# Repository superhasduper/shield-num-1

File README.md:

# shield-num-1
it is an Arduino shield pcb made in kicad

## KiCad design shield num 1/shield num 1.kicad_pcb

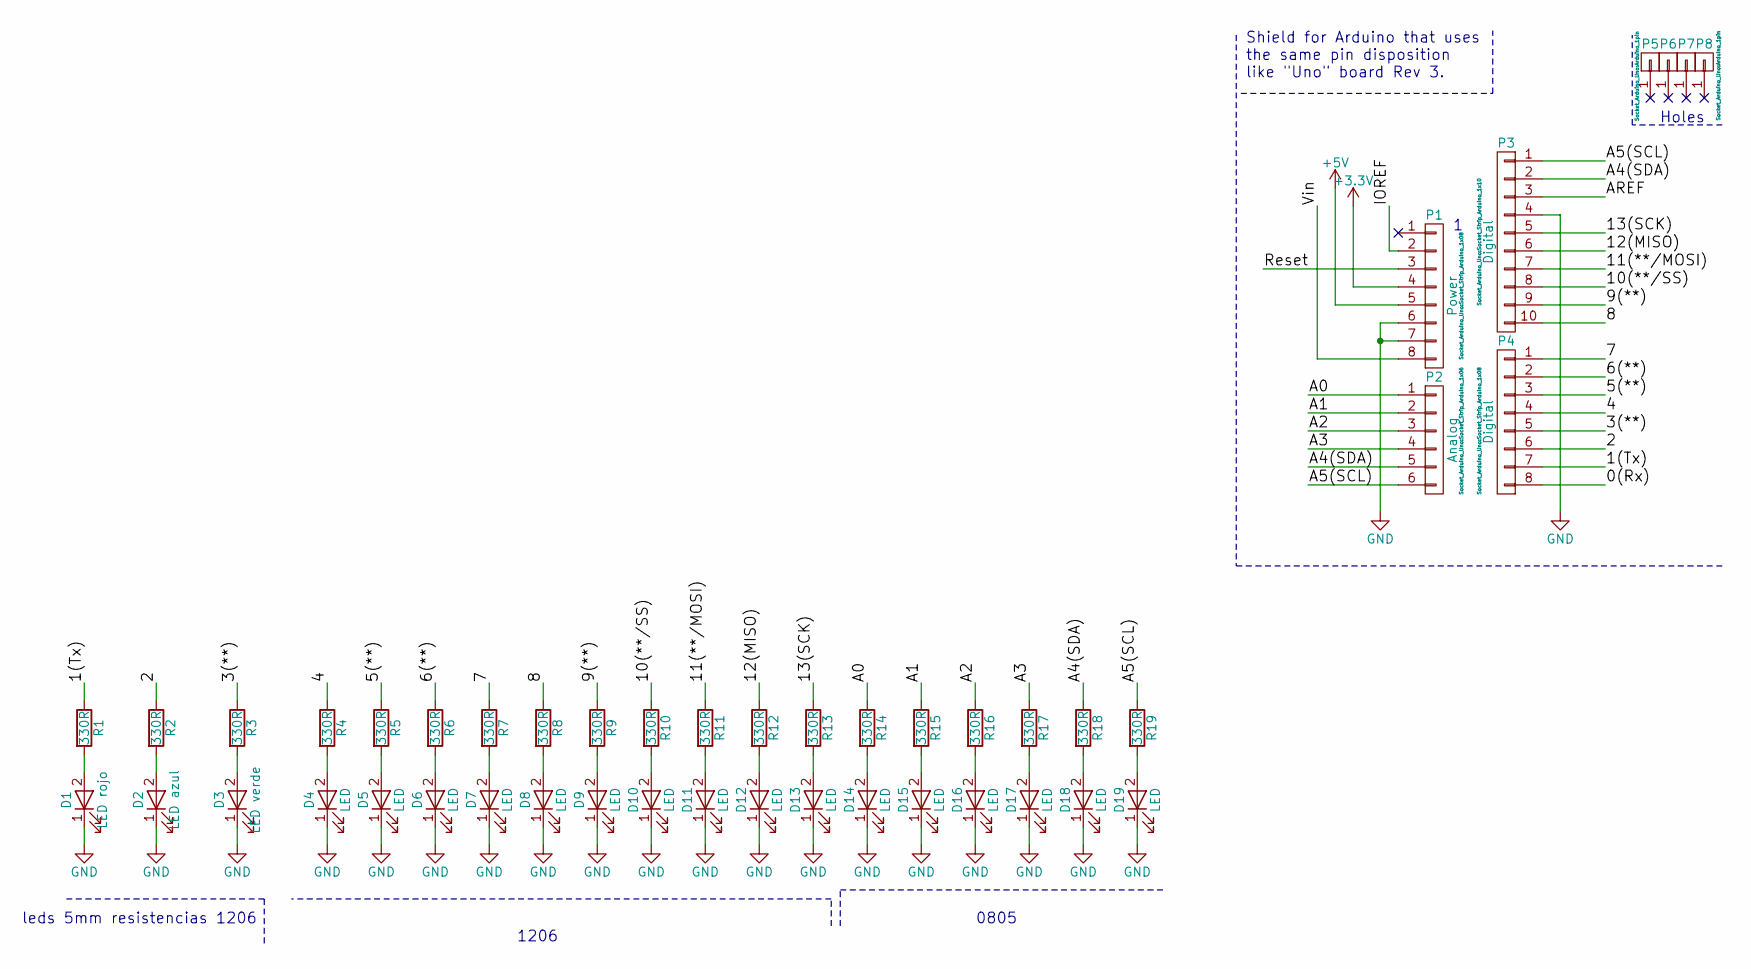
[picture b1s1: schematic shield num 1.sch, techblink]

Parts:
D1: LED rojo; LED_D5.0mm
D2: LED azul; LED_D5.0mm
D3: LED verde; LED_D5.0mm
D4, D5, D6, D7, D8, D9, D10, D11, D12, D13: LED; LED_1206_HandSoldering
D14, D15, D16, D17, D18, D19: LED; LED_0805_HandSoldering
P1: Power; Socket_Strip_Arduino_1x08
P2: Analog; Socket_Strip_Arduino_1x06
P3: Digital; Socket_Strip_Arduino_1x10
P4: Digital; Socket_Strip_Arduino_1x08
P5, P6, P7, P8: CONN_01X01; Arduino_1pin
R1, R2, R3, R4, R5, R6, R7, R8, R9, R10, R11, R12, R13: 330R; R_1206_HandSoldering
R14, R15, R16, R17, R18, R19: 330R; R_0805_HandSoldering

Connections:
+3V3: P1.4
+5V: P1.5
/0(Rx): P4.8
/1(Tx): P4.7, R1.1
/2: P4.6, R2.1
/3(**): P4.5, R3.1
/4: P4.4, R4.1
/5(**): P4.3, R5.1
/6(**): P4.2, R6.1
/7: P4.1, R7.1
/8: P3.10, R8.1
/9(**): P3.9, R9.1
/10(**/SS): P3.8, R10.1
/11(**/MOSI): P3.7, R11.1
/12(MISO): P3.6, R12.1
/13(SCK): P3.5, R13.1
/A0: P2.1, R14.1
/A1: P2.2, R15.1
/A2: P2.3, R16.1
/A3: P2.4, R17.1
/A4(SDA): P2.5, P3.2, R18.1
/A5(SCL): P2.6, P3.1, R19.1
/AREF: P3.3
/IOREF: P1.2
/Reset: P1.3
/Vin: P1.8
GND: D1.1 (K), D2.1 (K), D3.1 (K), D4.1 (K), D5.1 (K), D6.1 (K), D7.1 (K), D8.1 (K), D9.1 (K), D10.1 (K), D11.1 (K), D12.1 (K), D13.1 (K), D14.1 (K), D15.1 (K), D16.1 (K), D17.1 (K), D18.1 (K), D19.1 (K), P1.6, P1.7, P3.4
unnamed: D1.2 (A), R1.2
unnamed: D2.2 (A), R2.2
unnamed: D3.2 (A), R3.2
unnamed: D4.2 (A), R4.2
unnamed: D5.2 (A), R5.2
unnamed: D6.2 (A), R6.2
unnamed: D7.2 (A), R7.2
unnamed: D8.2 (A), R8.2
unnamed: D9.2 (A), R9.2
unnamed: D10.2 (A), R10.2
unnamed: D11.2 (A), R11.2
unnamed: D12.2 (A), R12.2
unnamed: D13.2 (A), R13.2
unnamed: D14.2 (A), R14.2
unnamed: D15.2 (A), R15.2
unnamed: D16.2 (A), R16.2
unnamed: D17.2 (A), R17.2
unnamed: D18.2 (A), R18.2
unnamed: D19.2 (A), R19.2

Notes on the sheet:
Holes
Shield for Arduino that uses the same pin disposition like "Uno" board Rev 3.
leds 5mm resistencias 1206
1206
0805

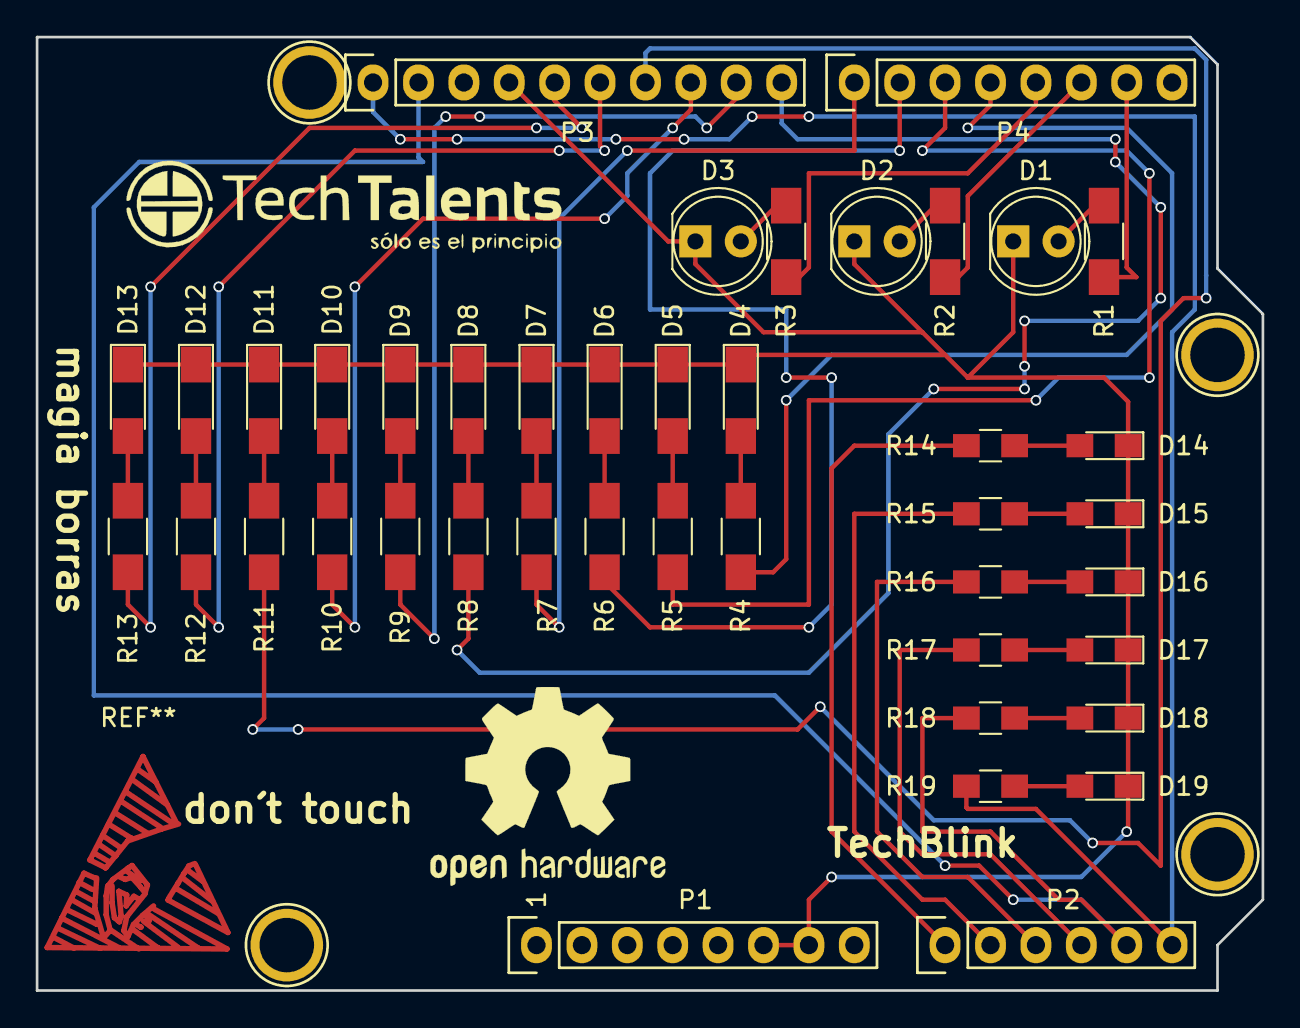
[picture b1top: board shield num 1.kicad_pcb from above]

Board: 2 copper layers, 68.6 x 53.3 mm, 46 parts (0 on the bottom side), 39 nets.

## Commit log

2019-07-07 here is everything
